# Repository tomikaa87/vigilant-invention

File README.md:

# vigilant-invention
This is just my playground repository where I store various hobby projects 

# ShutterMotorController
A simple IoT controller for electronic window shutter belt winders.

# ESPControlCenter
An attempt to make a small home automation control center with ESP8266.

# ChargeController
A smart plug build with an ESP8266 WiFi controller and a companion application for Android to turn on/off charging the phone automatically when the battery charge level reaches the given thresholds.

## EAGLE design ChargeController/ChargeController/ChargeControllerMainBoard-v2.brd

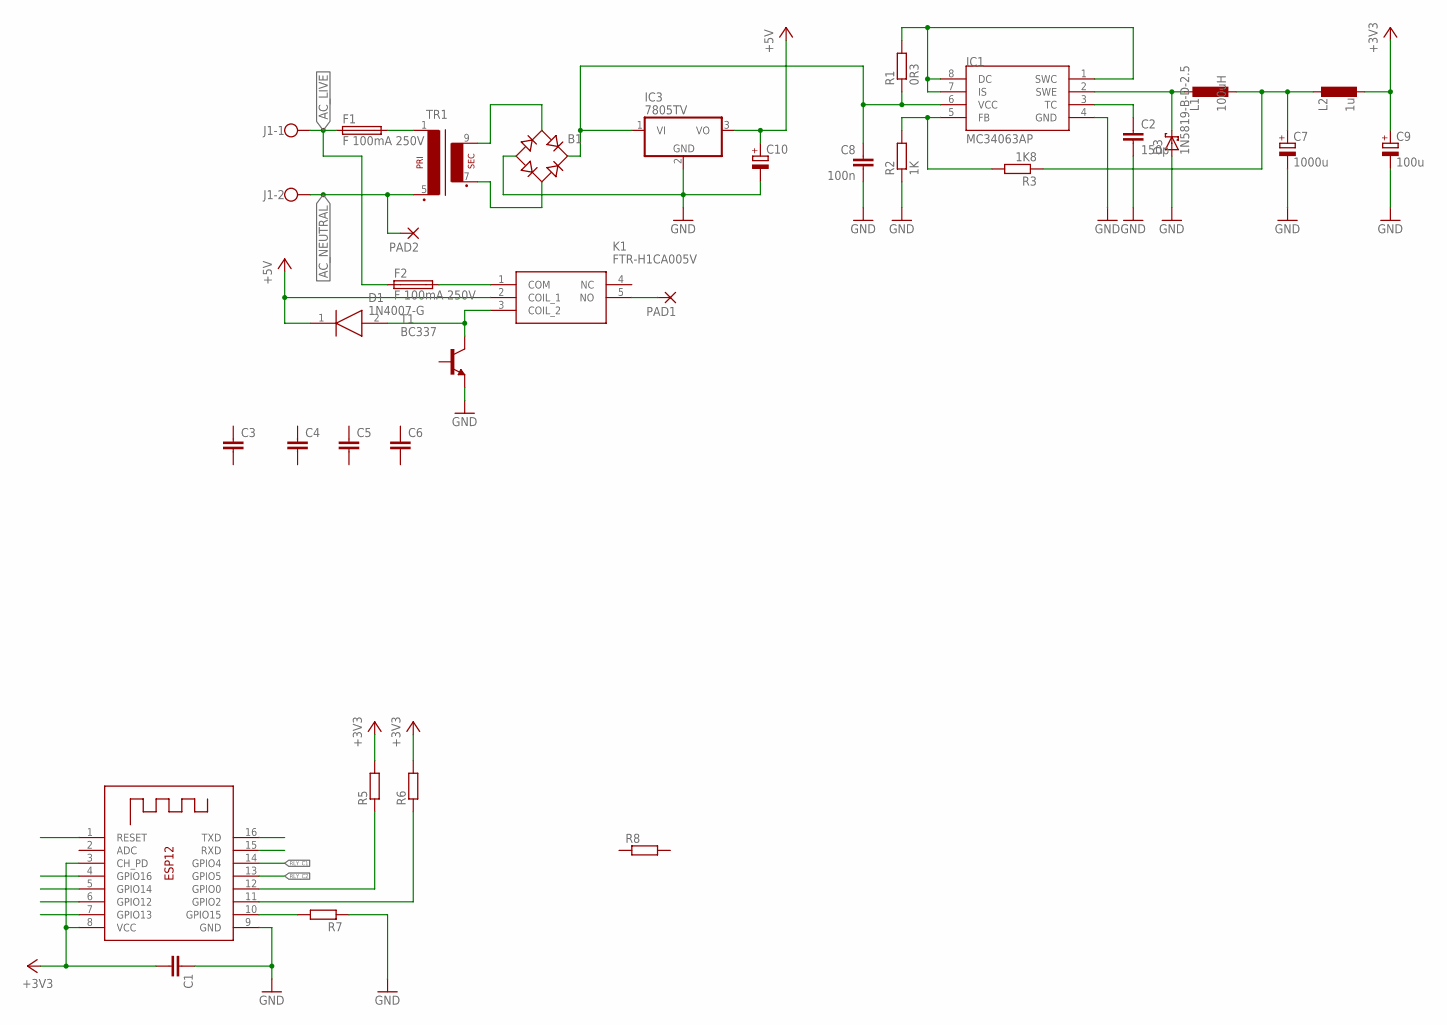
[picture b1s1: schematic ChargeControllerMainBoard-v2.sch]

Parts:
B1: B-DIL
C1, C3, C4, C5, C6: C-EUC0805; C0805
C2: 150p; C025-024X044
C7: 1000u; E3,5-8
C8: 100n; C025-024X044
C9: 100u; E3,5-8
C10: CPOL-EUE3.5-8; E3,5-8
D1: 1N4007-G; DIOAD1410W90L470D235
D3: 1N5819-B-D-2.5; D-2.5
F1, F2: F 100mA 250V; SH22,5
IC1: MC34063AP; DIL08
IC3: 7805TV; TO220V
J1: W237-102
K1: FTR-H1CA005V; FTRH1CA005V
L1: 100uH; 6000-XXXX-RC
L2: 1u; 0204V
PAD1, PAD2: 2,54/1,1
R1: 0R3; 0204V
R2: 1K; 0204V
R3: 1K8; 0204V
R5, R6, R7, R8: R-EU_R0805; R0805
T1: BC337; TO92
TR1: EI30-1
X1: ESP-12

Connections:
+3V3: C1.2, C9.+, L2.2, R5.2, R6.2, X1.3 (CH_PD), X1.8 (VCC)
+5V: C10.+, D1.1 (K), IC3.3 (VO), K1.2 (COIL_1)
AC_LIVE: F1.1, F2.1, J1.1
AC_NEUTRAL: J1.2, PAD2.1, TR1.5 (P2)
GND: B1.-, C1.1, C2.2, C7.-, C8.2, C9.-, C10.-, D3.A, IC1.4 (GND), IC3.2 (GND), R2.1, R7.1, T1.1 (E), X1.9 (GND)
unnamed: IC1.1 (SWC), IC1.7 (IS), IC1.8 (DC), R1.2
unnamed: IC1.5 (FB), R2.2, R3.2
unnamed: C2.1, IC1.3 (TC)
unnamed: D3.C, IC1.2 (SWE), L1.1
unnamed: B1.AC1, TR1.9 (S4)
unnamed: C7.+, L1.2, L2.1, R3.1
unnamed: K1.5 (NO), PAD1.1
unnamed: F2.2, K1.1 (COM)
unnamed: B1.AC2, TR1.7 (S3)
unnamed: D1.2 (A), K1.3 (COIL_2), T1.3 (C)
unnamed: R5.1, X1.12 (GPIO0)
unnamed: R6.1, X1.11 (GPIO2)
unnamed: R7.2, X1.10 (GPIO15)
unnamed: F1.2, TR1.1
unnamed: B1.+, C8.1, IC1.6 (VCC), IC3.1 (VI), R1.1
RLY_C1: X1.14 (GPIO4)
RLY_C2: X1.13 (GPIO5)

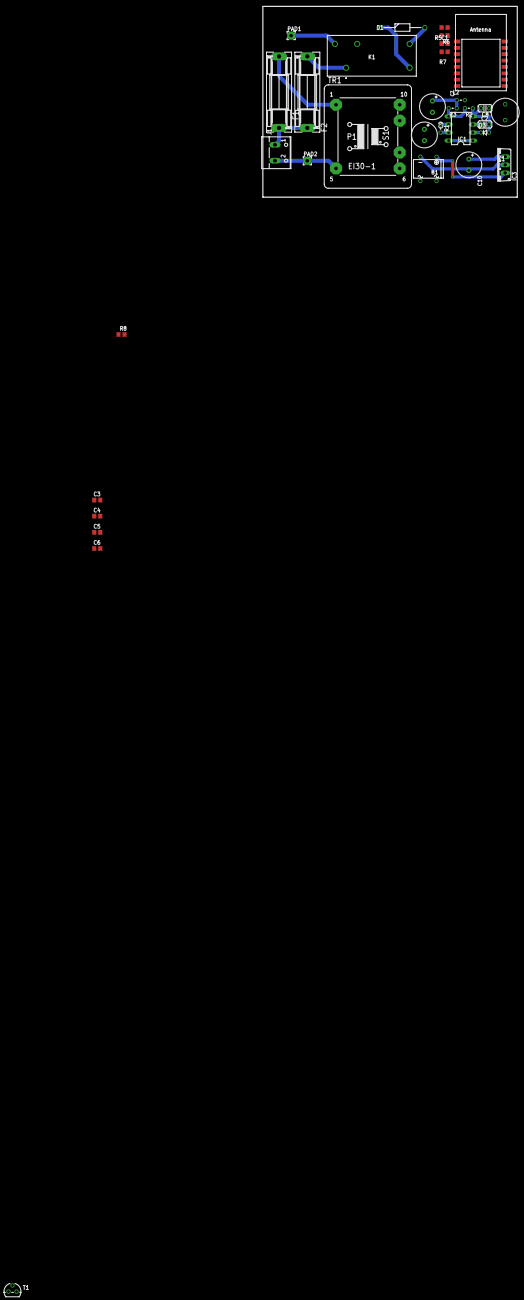
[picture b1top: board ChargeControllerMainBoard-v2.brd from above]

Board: 2 copper layers, 80.0 x 60.0 mm, 33 parts (0 on the bottom side), 20 nets.

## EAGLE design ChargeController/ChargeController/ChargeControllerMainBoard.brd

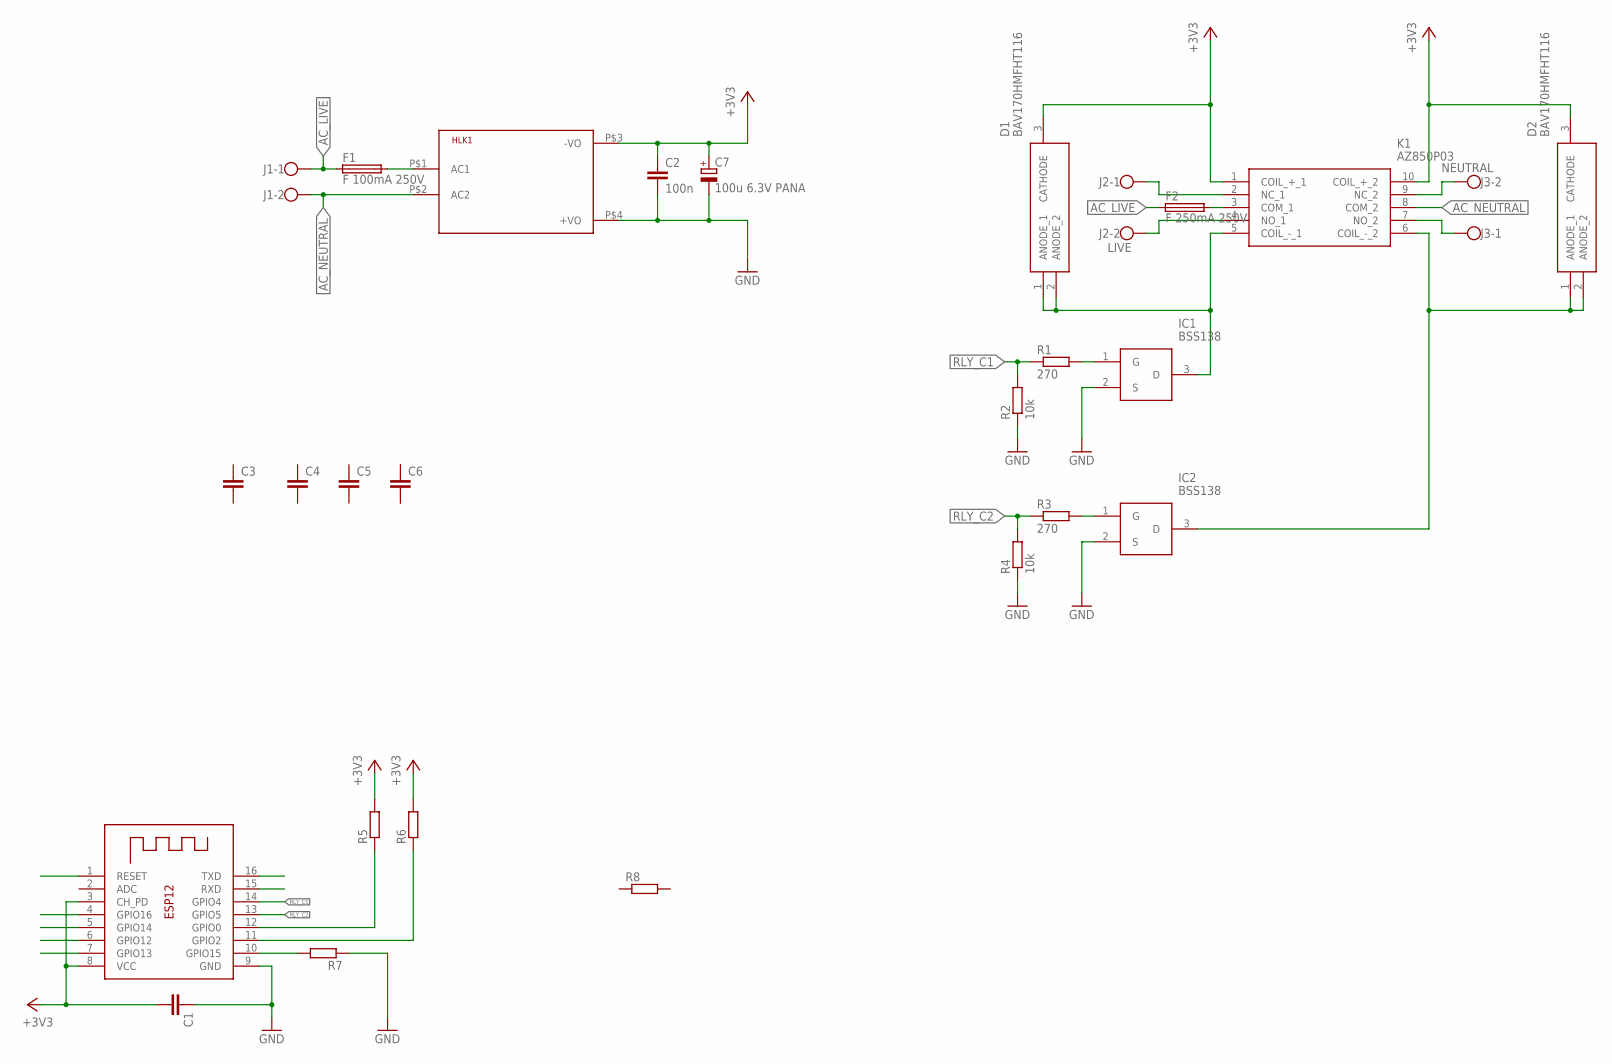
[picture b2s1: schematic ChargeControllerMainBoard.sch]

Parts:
C1, C3, C4, C5, C6: C-EUC0805; C0805
C2: 100n; C0805
C7: 100u 6.3V PANA; PANASONIC_B
D1, D2: BAV170HMFHT116; SOT95P240X115-3N
F1: F 100mA 250V; SH22,5
F2: F 250mA 250V; SH22,5
HLK1: HLK-PM03; HLK-PM01
IC1, IC2: BSS138; SOT95P240X120-3N
J1: W237-102
J2: LIVE; W237-102
J3: NEUTRAL; W237-102
K1: AZ850P03; DIPS763W51P254L1400H525Q10N
R1, R3: 270; R0805
R2, R4: 10k; R0805
R5, R6, R7, R8: R-EU_R0805; R0805
X1: ESP-12

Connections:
+3V3: C1.2, C2.1, C7.+, D1.3 (CATHODE), D2.3 (CATHODE), HLK1.P$3 (-VO), K1.1 (COIL_+_1), K1.10 (COIL_+_2), R5.2, R6.2, X1.3 (CH_PD), X1.8 (VCC)
AC_LIVE: F1.1, F2.1, J1.1
AC_NEUTRAL: HLK1.P$2 (AC2), J1.2, K1.8 (COM_2)
GND: C1.1, C2.2, C7.-, HLK1.P$4 (+VO), IC1.2 (S), IC2.2 (S), R2.1, R4.1, R7.1, X1.9 (GND)
unnamed: IC2.1 (G), R3.2
unnamed: D1.1 (ANODE_1), D1.2 (ANODE_2), IC1.3 (D), K1.5 (COIL_-_1)
unnamed: IC1.1 (G), R1.2
unnamed: D2.1 (ANODE_1), D2.2 (ANODE_2), IC2.3 (D), K1.6 (COIL_-_2)
unnamed: J2.1, K1.2 (NC_1)
unnamed: J2.2, K1.4 (NO_1)
unnamed: J3.2, K1.9 (NC_2)
unnamed: J3.1, K1.7 (NO_2)
unnamed: R5.1, X1.12 (GPIO0)
unnamed: R6.1, X1.11 (GPIO2)
unnamed: R7.2, X1.10 (GPIO15)
unnamed: F1.2, HLK1.P$1 (AC1)
unnamed: F2.2, K1.3 (COM_1)
RLY_C1: R1.1, R2.2, X1.14 (GPIO4)
RLY_C2: R3.1, R4.2, X1.13 (GPIO5)

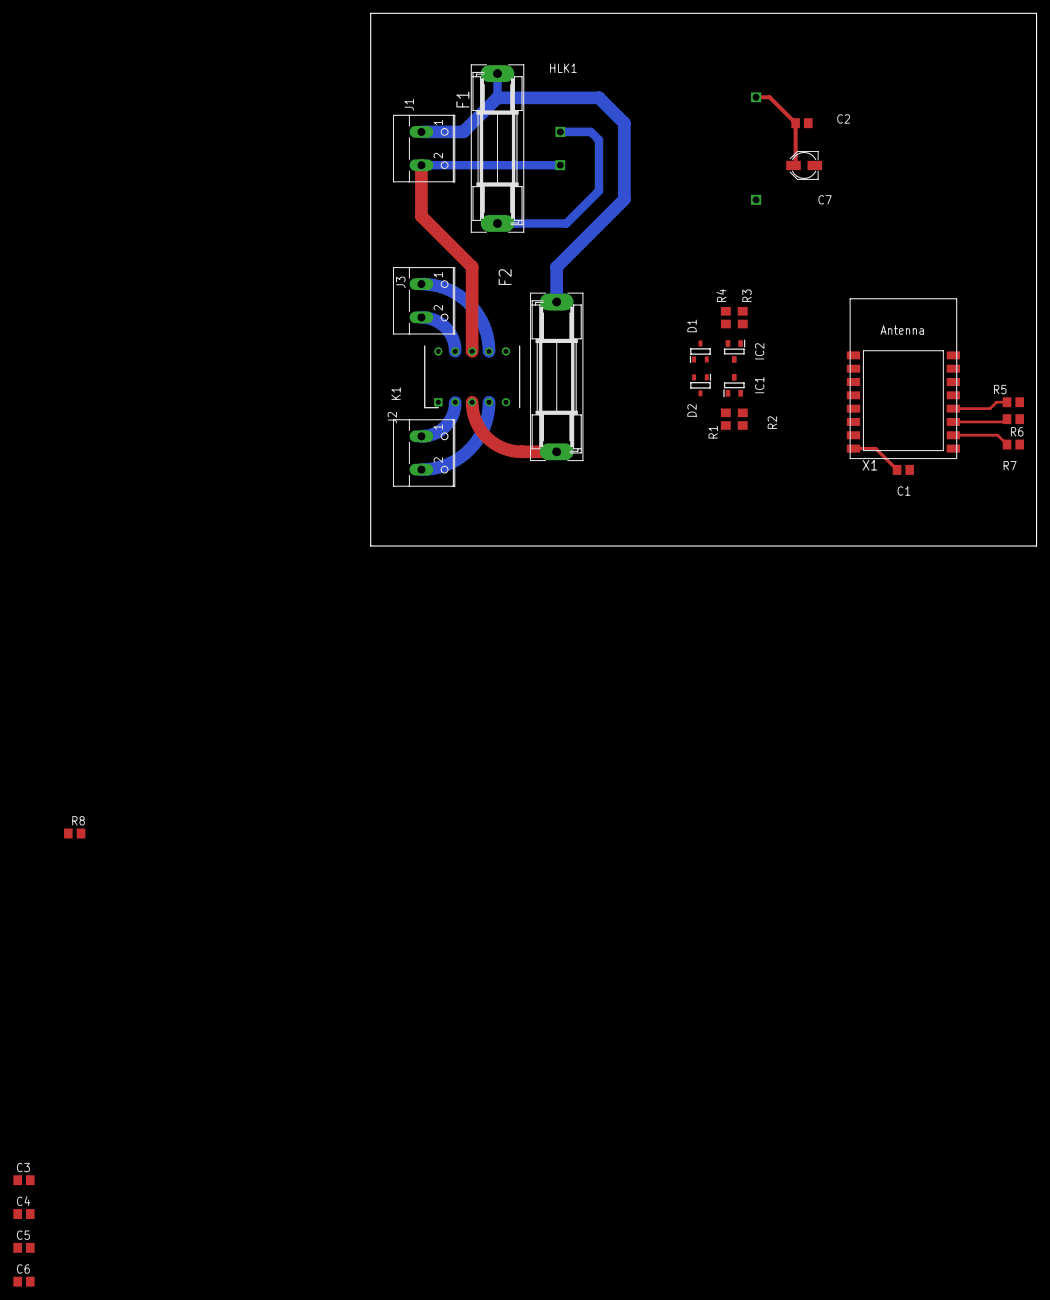
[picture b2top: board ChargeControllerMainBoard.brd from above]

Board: 2 copper layers, 100.0 x 80.0 mm, 27 parts (0 on the bottom side), 19 nets.

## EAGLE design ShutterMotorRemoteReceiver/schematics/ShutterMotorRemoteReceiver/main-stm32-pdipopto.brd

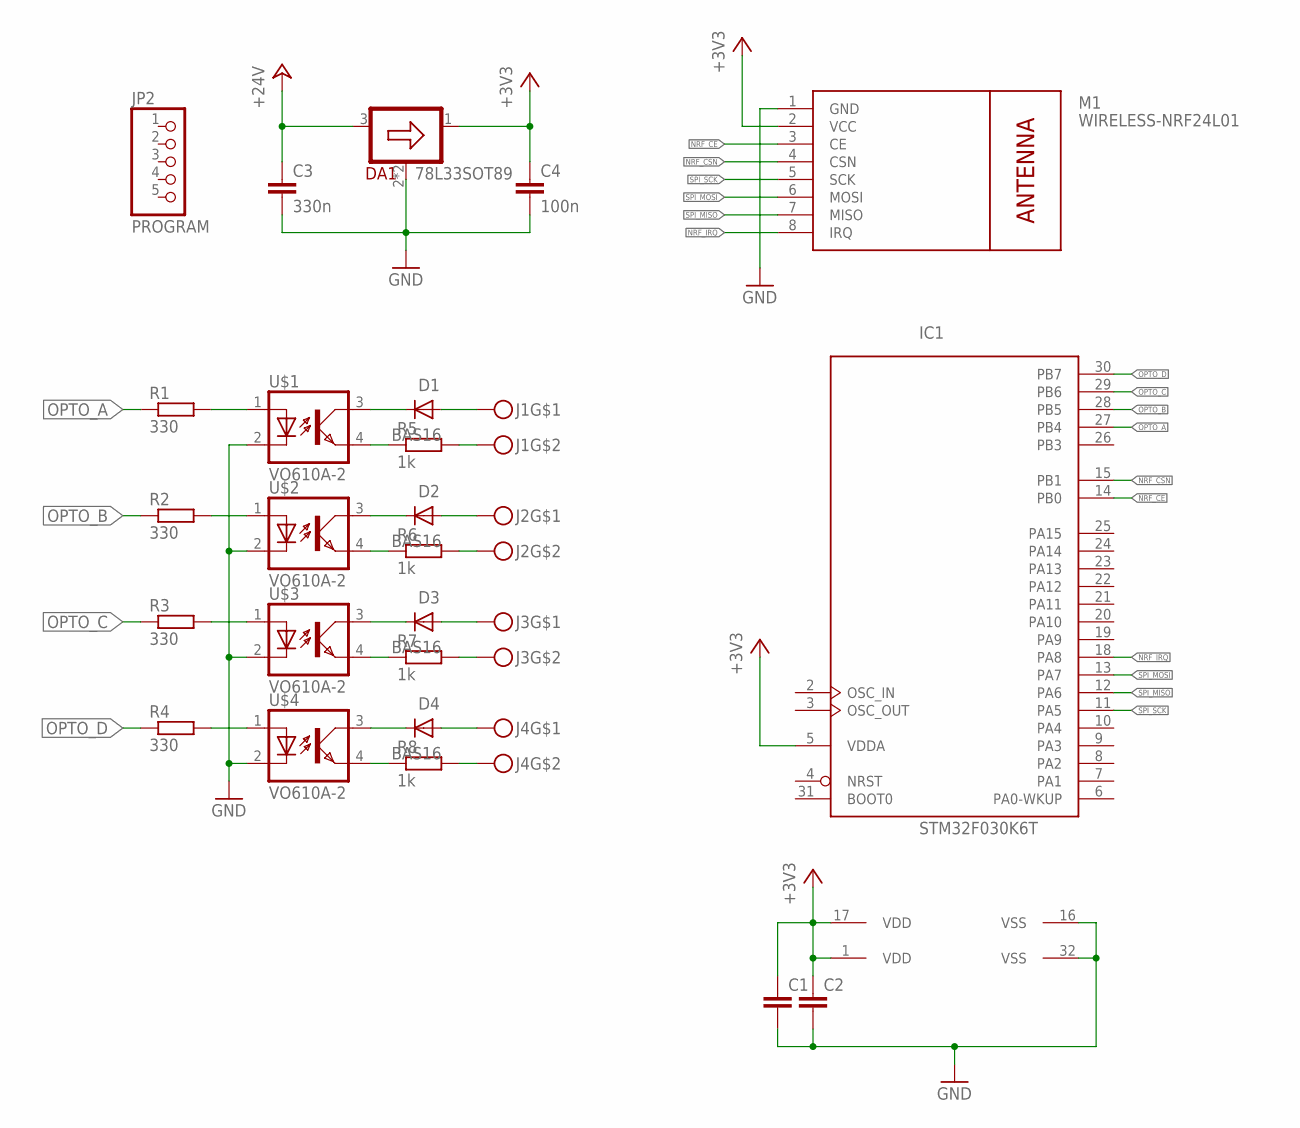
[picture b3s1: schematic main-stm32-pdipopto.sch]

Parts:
C1, C2: C-EUC1206; C1206
C3: 330n; C1206
C4: 100n; C1206
D1, D2, D3, D4: BAS16; SOT23
DA1: 78L33SOT89; SOT89
IC1: STM32F030K6T; LQFP32
J1, J2, J3, J4: SCREW-TERMINAL-2PIN; PITCH4.3-PIN2
JP2: PROGRAM; 1X05
M1: WIRELESS-NRF24L01
R1, R2, R3, R4: 330; R1206
R5, R6, R7, R8: 1k; R1206
U$1, U$2, U$3, U$4: VO610A-2; DIL04

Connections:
+3V3: C1.1, C2.1, C4.1, DA1.1 (OUT), IC1.1 (VDD), IC1.5 (VDDA), IC1.17 (VDD), M1.2 (VCC)
+24V: C3.1, DA1.3 (IN)
GND: C1.2, C2.2, C3.2, C4.2, DA1.2 (GND), DA1.2@1 (GND), IC1.16 (VSS), IC1.32 (VSS), M1.1 (GND), U$1.2 (C), U$2.2 (C), U$3.2 (C), U$4.2 (C)
unnamed: R5.1, U$1.4 (EMIT)
unnamed: J1.2, R5.2
unnamed: R1.2, U$1.1 (A)
unnamed: R2.2, U$2.1 (A)
unnamed: D1.3 (K), U$1.3 (COL)
unnamed: D2.3 (K), U$2.3 (COL)
unnamed: D3.3 (K), U$3.3 (COL)
unnamed: D4.3 (K), U$4.3 (COL)
unnamed: D1.1 (A), J1.1
unnamed: R6.1, U$2.4 (EMIT)
unnamed: D2.1 (A), J2.1
unnamed: J2.2, R6.2
unnamed: D3.1 (A), J3.1
unnamed: R7.1, U$3.4 (EMIT)
unnamed: D4.1 (A), J4.1
unnamed: J3.2, R7.2
unnamed: R3.2, U$3.1 (A)
unnamed: R4.2, U$4.1 (A)
unnamed: R8.1, U$4.4 (EMIT)
unnamed: J4.2, R8.2
NRF_CE: IC1.14 (PB0), M1.3 (CE)
NRF_CSN: IC1.15 (PB1), M1.4 (CSN)
NRF_IRQ: IC1.18 (PA8), M1.8 (IRQ)
OPTO_A: IC1.27 (PB4), R1.1
OPTO_B: IC1.28 (PB5), R2.1
OPTO_C: IC1.29 (PB6), R3.1
OPTO_D: IC1.30 (PB7), R4.1
SPI_MISO: IC1.12 (PA6), M1.7 (MISO)
SPI_MOSI: IC1.13 (PA7), M1.6 (MOSI)
SPI_SCK: IC1.11 (PA5), M1.5 (SCK)

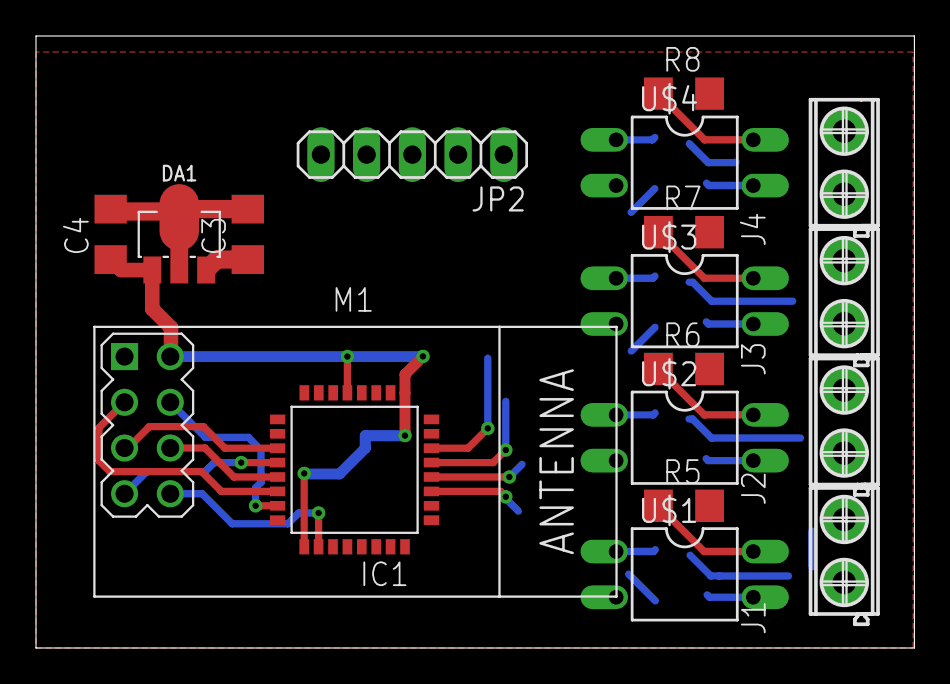
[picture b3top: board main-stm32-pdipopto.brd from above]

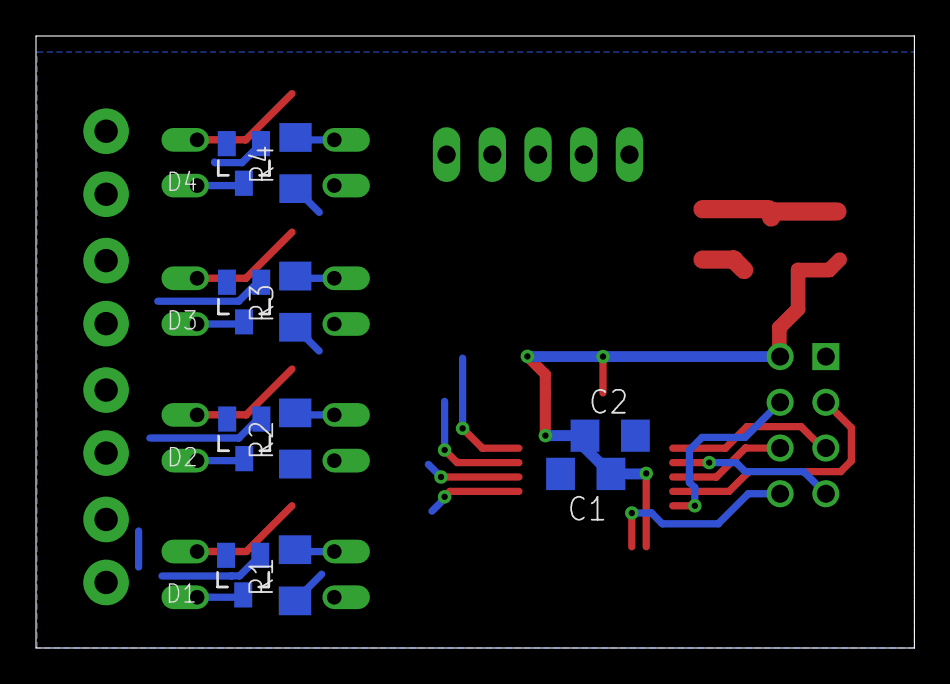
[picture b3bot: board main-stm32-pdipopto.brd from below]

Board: 2 copper layers, 48.8 x 34.0 mm, 28 parts (10 on the bottom side), 33 nets.

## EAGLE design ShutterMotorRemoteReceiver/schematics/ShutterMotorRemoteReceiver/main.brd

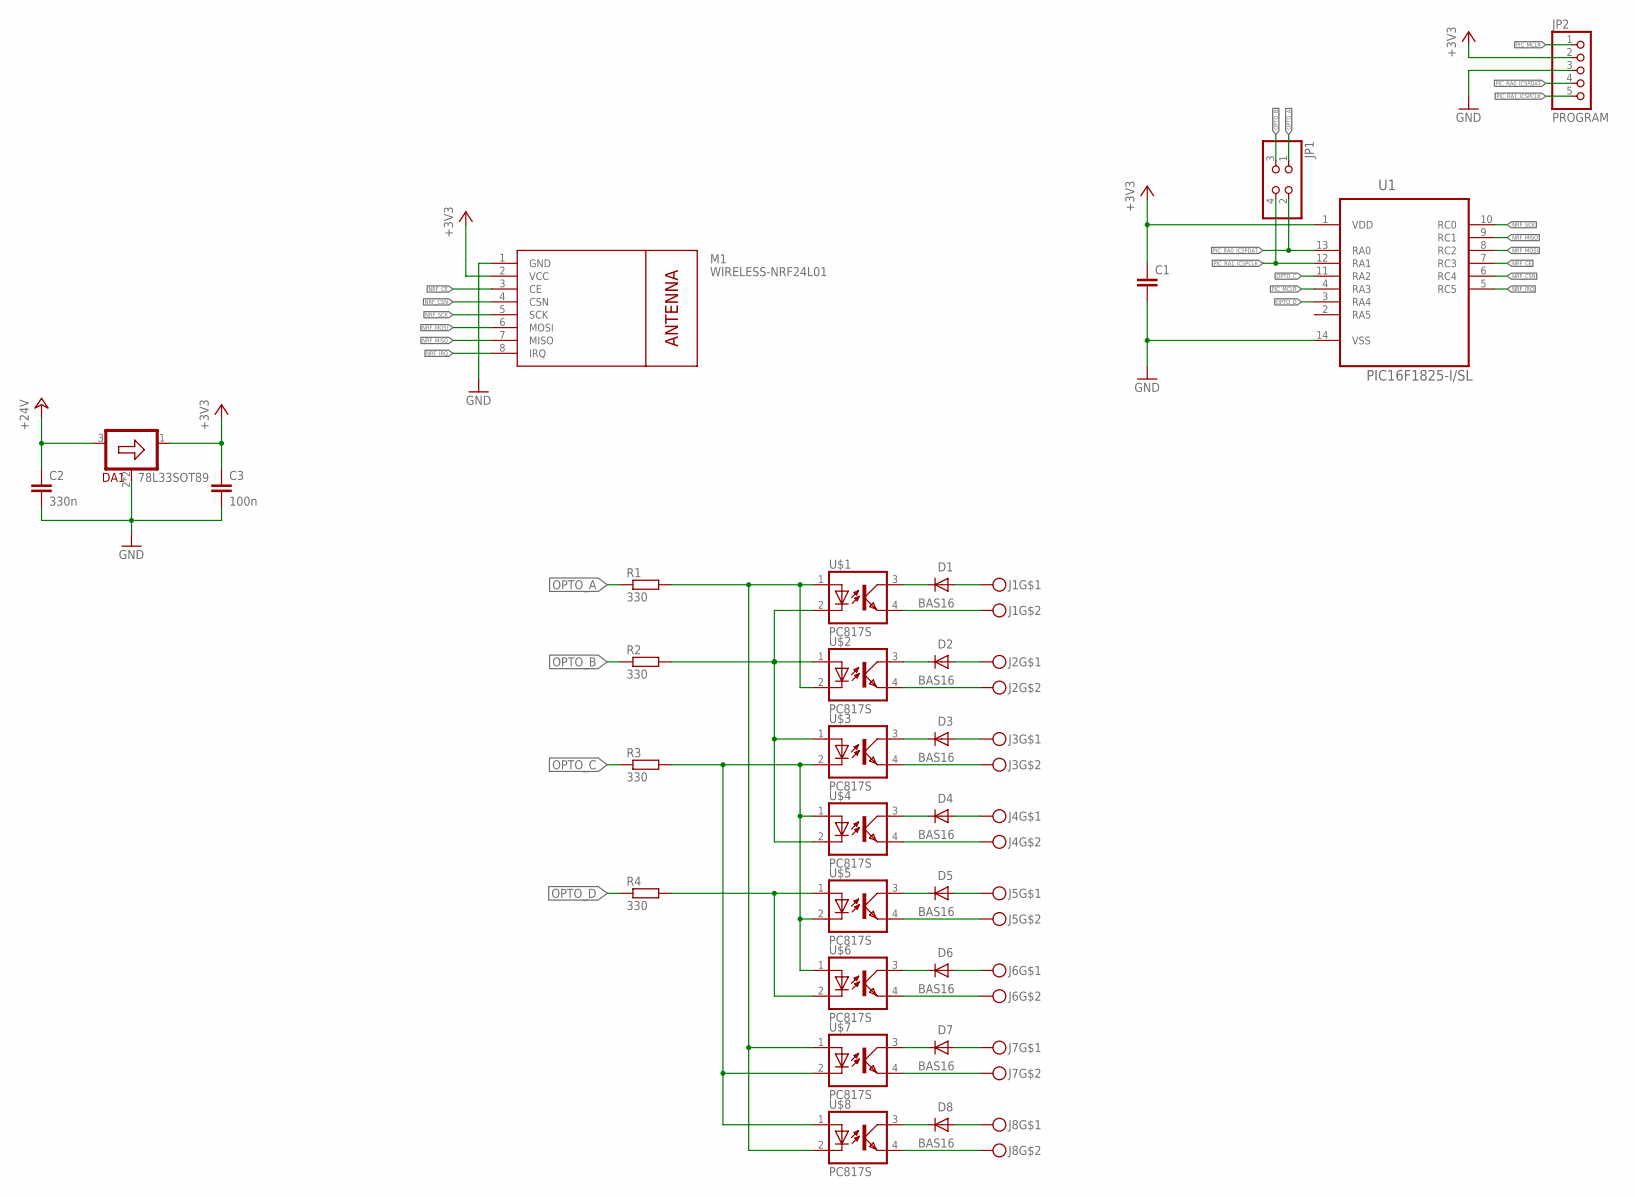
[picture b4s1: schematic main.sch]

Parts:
C1: C-EUC1206; C1206
C2: 330n; C1206
C3: 100n; C1206
D1, D2, D3, D4, D5, D6, D7, D8: BAS16; SOT23
DA1: 78L33SOT89; SOT89
J1, J2, J3, J4, J5, J6, J7, J8: SCREW-TERMINAL-2PIN; PITCH4.3-PIN2
JP1: PINHD-2X2; 2X02
JP2: PROGRAM; 1X05
M1: WIRELESS-NRF24L01
R1, R2, R3, R4: 330; R1206
U1: PIC16F1825-I/SL; SOIC127P600X175-14N
U$1, U$2, U$3, U$4, U$5, U$6, U$7, U$8: PC817S; SMD4-7

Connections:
+3V3: C1.1, C3.1, DA1.1 (OUT), JP2.2, M1.2 (VCC), U1.1 (VDD)
+24V: C2.1, DA1.3 (IN)
GND: C1.2, C2.2, C3.2, DA1.2 (GND), DA1.2@1 (GND), JP2.3, M1.1 (GND), U1.14 (VSS)
unnamed: R2.2, U$1.2 (C), U$2.1 (A), U$3.1 (A), U$4.2 (C)
unnamed: R1.2, U$1.1 (A), U$2.2 (C), U$7.1 (A), U$8.2 (C)
unnamed: R3.2, U$3.2 (C), U$4.1 (A), U$5.2 (C), U$6.1 (A), U$7.2 (C), U$8.1 (A)
unnamed: R4.2, U$5.1 (A), U$6.2 (C)
unnamed: D1.3 (K), U$1.3 (COL)
unnamed: D2.3 (K), U$2.3 (COL)
unnamed: D3.3 (K), U$3.3 (COL)
unnamed: D4.3 (K), U$4.3 (COL)
unnamed: D1.1 (A), J1.1
unnamed: J1.2, U$1.4 (EMIT)
unnamed: D2.1 (A), J2.1
unnamed: J2.2, U$2.4 (EMIT)
unnamed: D3.1 (A), J3.1
unnamed: J3.2, U$3.4 (EMIT)
unnamed: D4.1 (A), J4.1
unnamed: J4.2, U$4.4 (EMIT)
unnamed: D5.3 (K), U$5.3 (COL)
unnamed: D6.3 (K), U$6.3 (COL)
unnamed: D7.3 (K), U$7.3 (COL)
unnamed: D8.3 (K), U$8.3 (COL)
unnamed: D5.1 (A), J5.1
unnamed: J5.2, U$5.4 (EMIT)
unnamed: D6.1 (A), J6.1
unnamed: J6.2, U$6.4 (EMIT)
unnamed: D7.1 (A), J7.1
unnamed: J7.2, U$7.4 (EMIT)
unnamed: D8.1 (A), J8.1
unnamed: J8.2, U$8.4 (EMIT)
NRF_CE: M1.3 (CE), U1.7 (RC3)
NRF_CSN: M1.4 (CSN), U1.6 (RC4)
NRF_IRQ: M1.8 (IRQ), U1.5 (RC5)
NRF_MISO: M1.7 (MISO), U1.9 (RC1)
NRF_MOSI: M1.6 (MOSI), U1.8 (RC2)
NRF_SCK: M1.5 (SCK), U1.10 (RC0)
OPTO_A: JP1.1, R1.1
OPTO_B: JP1.3, R2.1
OPTO_C: R3.1, U1.11 (RA2)
OPTO_D: R4.1, U1.3 (RA4)
PIC_MCLR: JP2.1, U1.4 (RA3)
PIC_RA0_ICSPDAT: JP1.2, JP2.4, U1.13 (RA0)
PIC_RA1_ICSPCLK: JP1.4, JP2.5, U1.12 (RA1)

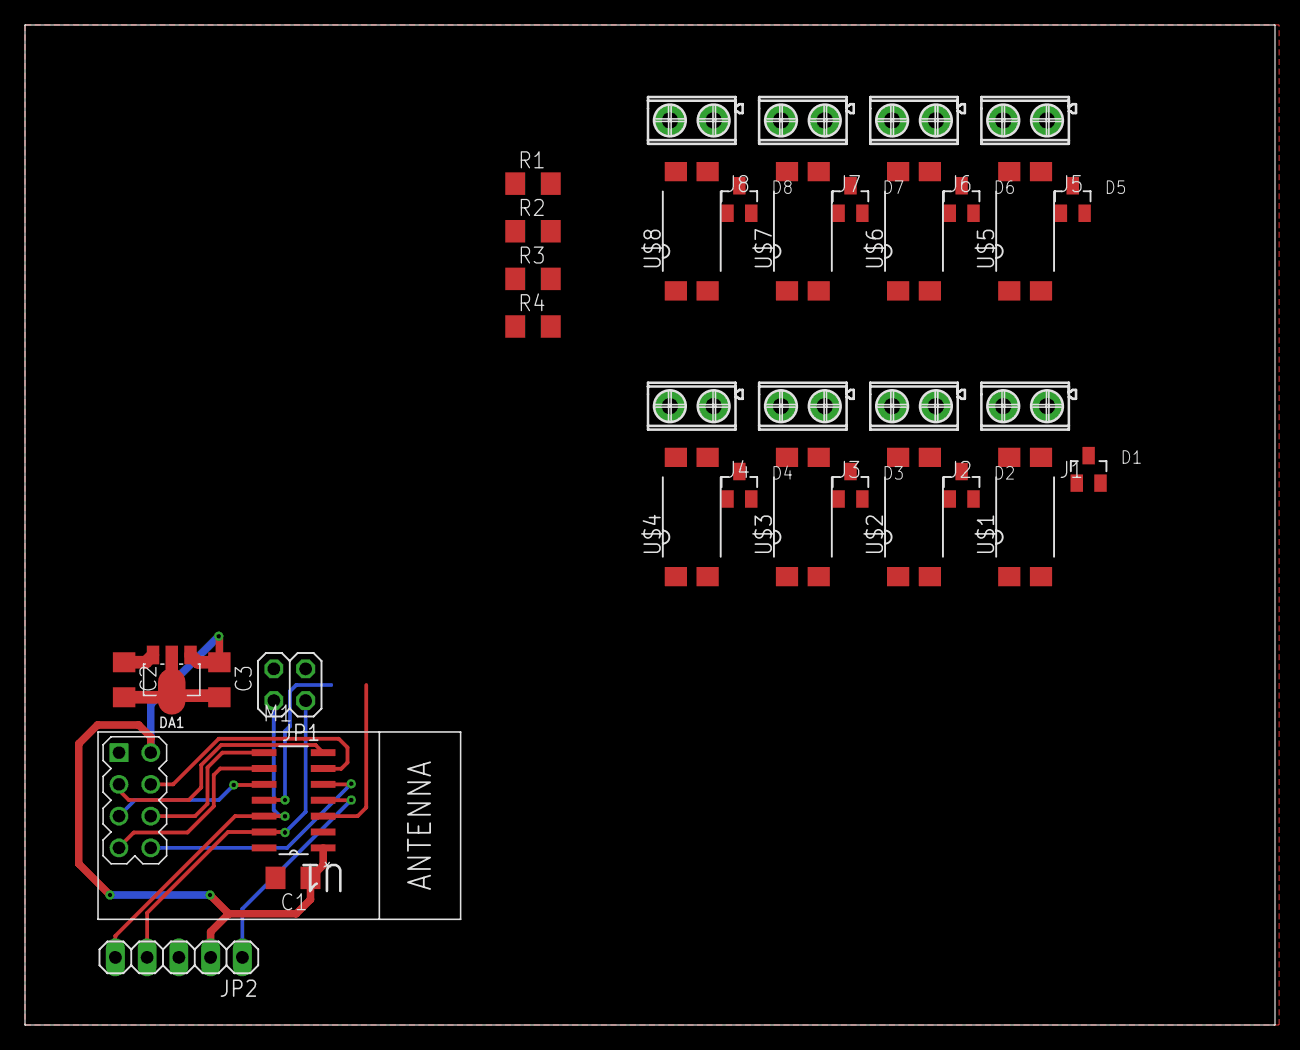
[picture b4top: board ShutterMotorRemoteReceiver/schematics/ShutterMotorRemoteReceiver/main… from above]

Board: 2 copper layers, 100.0 x 80.0 mm, 36 parts (0 on the bottom side), 44 nets.

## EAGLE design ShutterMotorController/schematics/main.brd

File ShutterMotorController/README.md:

# Shutter Motor Controller

As the name suggests, this project is about a connected controller for window shutter motors. 
It includes the schematics and PCB design as well as the firmware for the on-board ESP-12F 
module which was written in C++ using PlatformIO. As for the IoT part I have used Blynk but
the software is (in my opinion) well-modularized and easily be modified for other needs.

The firmware utilizes an NTP-controlled timer which can automatically open and close your
shutters (or control your connected appliance).

The controller has 4 reed relays so virtually it can interact with anything which has buttons
or any simple interface which can be driven by relays.

In my implementation I used 2 of these: https://www.amazon.de/gp/product/B074P186FX

They are reasonably cheap and can be easily modified to interface with the controller 
by soldering a thin 4-wire ribbon cable to the test pads on the PCB of the up and down 
buttons and connecting them to the relays. The software has functions to pulse the relays 
simulating a button press.

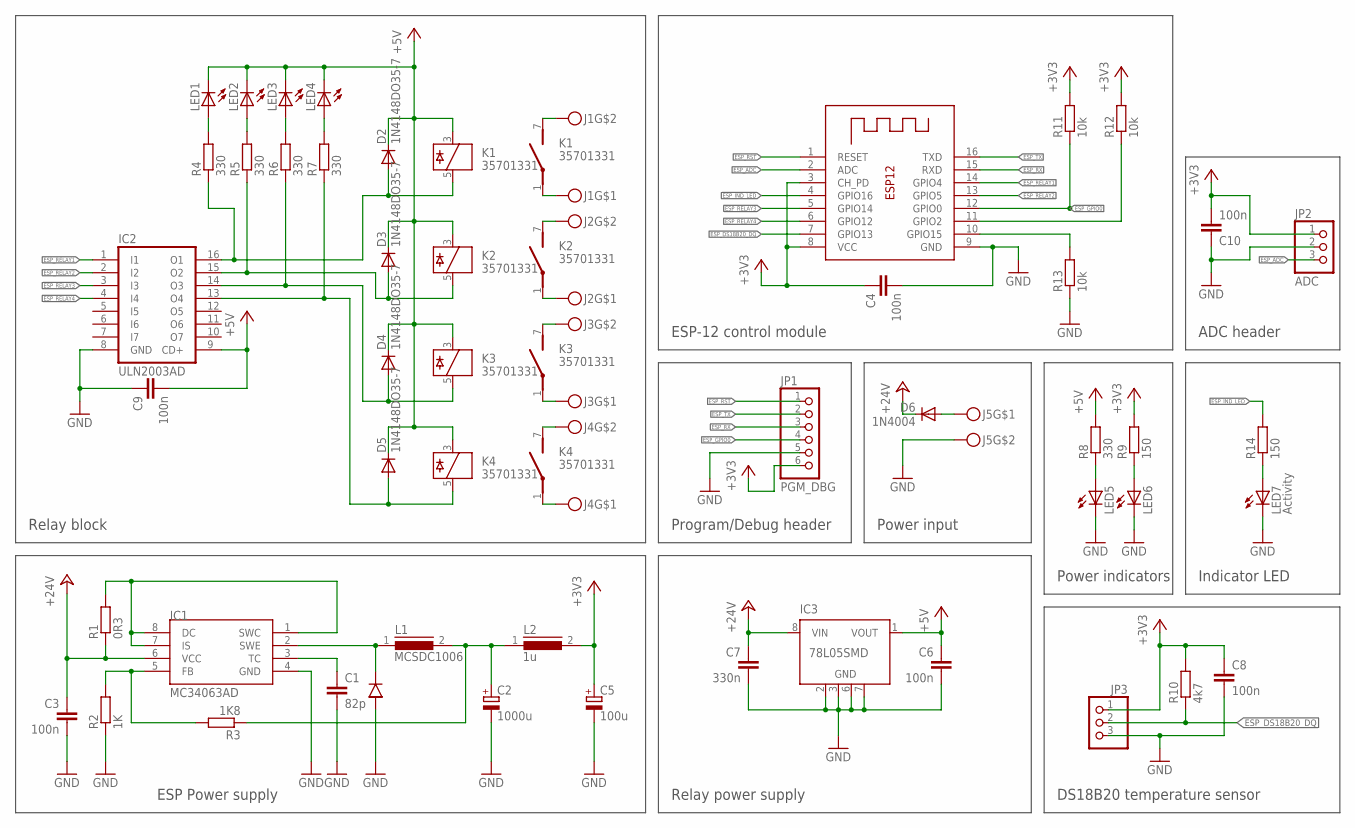
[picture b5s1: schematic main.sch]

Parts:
C1: 82p; C1206
C2: 1000u; UD-10X10_NICHICON
C3, C4, C6, C8, C9, C10: 100n; C1206
C5: 100u; 153CLV-0807
C7: 330n; C1206
D1: 1N5819HW; SOD123
D2, D3, D4, D5: 1N4148DO35-7; DO35-7
D6: 1N4004; DO41-10
IC1: MC34063AD; SOIC8
IC2: ULN2003AD; SO16
IC3: 78L05SMD; SO08
J1, J2, J3, J4: SCREW-TERMINAL-2PIN; PITCH4.3-PIN2
J5: PWR_IN; PITCH4.3-PIN2
JP1: PGM_DBG; 1X06
JP2: ADC; 1X03
JP3: PINHD-1X3; 1X03
K1, K2, K3, K4: 35701331; REED
L1: MCSDC1006; SMD
L2: 1u; R1210
LED1, LED2, LED3, LED4, LED5, LED6: LED5MM
LED7: Activity; LED5MM
R1: 0R3; R1206
R2: 1K; R1206
R3: 1K8; R1206
R4, R5, R6, R7, R8: 330; R1206
R9, R14: 150; R1206
R10: 4k7; R1206
R11, R12, R13: 10k; R1206
X1: ESP-12

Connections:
+3V3: C4.1, C5.+, C8.1, C10.2, JP1.6, JP2.1, JP3.1, L2.2, R9.2, R10.2, R11.2, R12.2, X1.3 (CH_PD), X1.8 (VCC)
+5V: C6.1, C9.2, D2.C, D3.C, D4.C, D5.C, IC2.9 (CD+), IC3.1 (VOUT), K1.3, K2.3, K3.3, K4.3, LED1.K (C), LED2.K (C), LED3.K (C), LED4.K (C), R8.2
+24V: C3.1, C7.1, D6.C, IC1.6 (VCC), IC3.8 (VIN), R1.1
ESP_ADC: JP2.3, X1.2 (ADC)
ESP_DS18B20_DQ: JP3.2, R10.1, X1.7 (GPIO13)
ESP_GPIO0: JP1.4, R11.1, X1.12 (GPIO0)
ESP_IND_LED: R14.2, X1.4 (GPIO16)
ESP_RELAY1: IC2.1 (I1), X1.14 (GPIO4)
ESP_RELAY2: IC2.2 (I2), X1.13 (GPIO5)
ESP_RELAY3: IC2.3 (I3), X1.5 (GPIO14)
ESP_RELAY4: IC2.4 (I4), X1.6 (GPIO12)
ESP_RST: JP1.1, X1.1 (RESET)
ESP_RX: JP1.3, X1.15 (RXD)
ESP_TX: JP1.2, X1.16 (TXD)
GND: C1.2, C2.-, C3.2, C4.2, C5.-, C6.2, C7.2, C8.2, C9.1, C10.1, D1.A, IC1.4 (GND), IC2.8 (GND), IC3.2 (GND), IC3.3 (GND), IC3.6 (GND), IC3.7 (GND), J5.2, JP1.5, JP2.2, JP3.3, LED5.K (C), LED6.K (C), LED7.K (C), R2.1, R13.1, X1.9 (GND)
unnamed: IC1.1 (SWC), IC1.7 (IS), IC1.8 (DC), R1.2
unnamed: C1.1, IC1.3 (TC)
unnamed: J1.2, K1.7 (S)
unnamed: D1.C, IC1.2 (SWE), L1.1
unnamed: IC1.5 (FB), R2.2, R3.2
unnamed: J1.1, K1.1
unnamed: J2.2, K2.7 (S)
unnamed: J2.1, K2.1
unnamed: D2.A, IC2.16 (O1), K1.5, R4.1
unnamed: D3.A, IC2.15 (O2), K2.5, R5.1
unnamed: J3.2, K3.7 (S)
unnamed: D5.A, IC2.13 (O4), K4.5, R7.1
unnamed: J3.1, K3.1
unnamed: D6.A, J5.1
unnamed: J4.2, K4.7 (S)
unnamed: J4.1, K4.1
unnamed: C2.+, L1.2, L2.1, R3.1
unnamed: LED1.A, R4.2
unnamed: D4.A, IC2.14 (O3), K3.5, R6.1
unnamed: LED2.A, R5.2
unnamed: LED3.A, R6.2
unnamed: LED4.A, R7.2
unnamed: LED5.A, R8.1
unnamed: LED6.A, R9.1
unnamed: R12.1, X1.11 (GPIO2)
unnamed: R13.2, X1.10 (GPIO15)
unnamed: LED7.A, R14.1

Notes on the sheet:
ESP Power supply
Relay block
Program/Debug header
ESP-12 control module
Power input
Relay power supply
Power indicators
DS18B20 temperature sensor
Indicator LED
ADC header

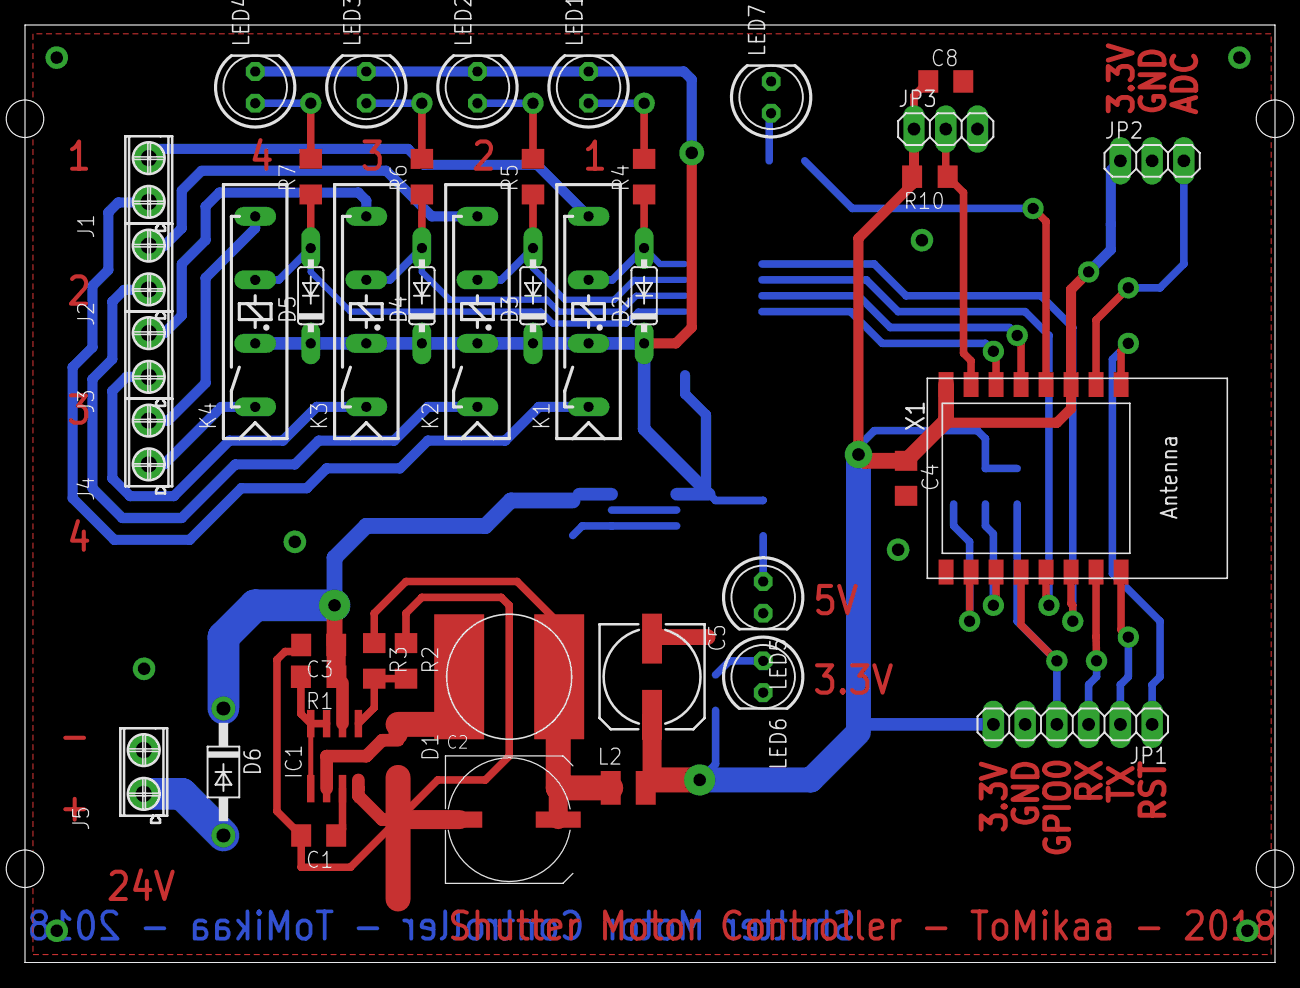
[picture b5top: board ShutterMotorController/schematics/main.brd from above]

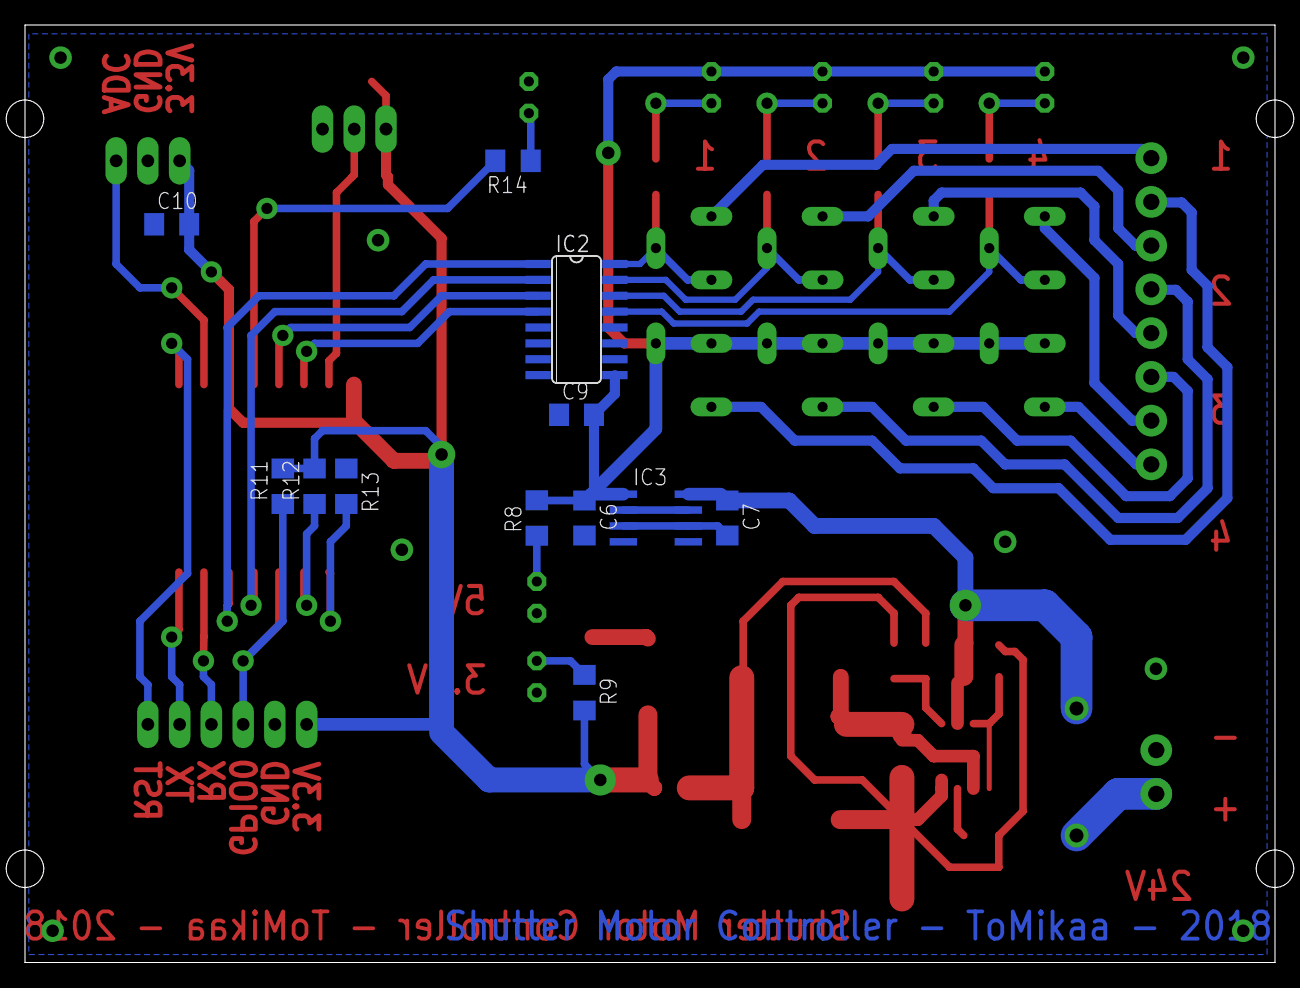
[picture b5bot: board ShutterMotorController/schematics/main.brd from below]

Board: 2 copper layers, 100.0 x 75.0 mm, 55 parts (12 on the bottom side), 42 nets.

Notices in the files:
FlowerGuard.X/mcc_generated_files/pin_manager.h:
(c) 2018 Microchip Technology Inc. and its subsidiaries.
parts and their libraries:
SparkFun-Switches: Licensing: Creative Commons ShareAlike 4.0 International - https://creativecommons.org/licenses/by-sa/4.0
diy-modules: Released under the Creative Commons Attribution 4.0 International License: http://creativecommons.org/licenses/by/4.0
